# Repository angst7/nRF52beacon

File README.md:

#nRF52beacon#

nRF52832 based beacon design

Simple reference design in a 1"x1.2" form factor with CR2032 battery holder.  For maximum battery life, ditch protection 
diode D2 and replace it with a FET (or just a jumper).  Tested to work with examples from the nRF52 SDK v11.0.0, but no
guarantees as to the effectiveness of the antenna.  

##License##

This work is licensed under [CC Attribution 3.0 United States](https://creativecommons.org/licenses/by/3.0/us/).

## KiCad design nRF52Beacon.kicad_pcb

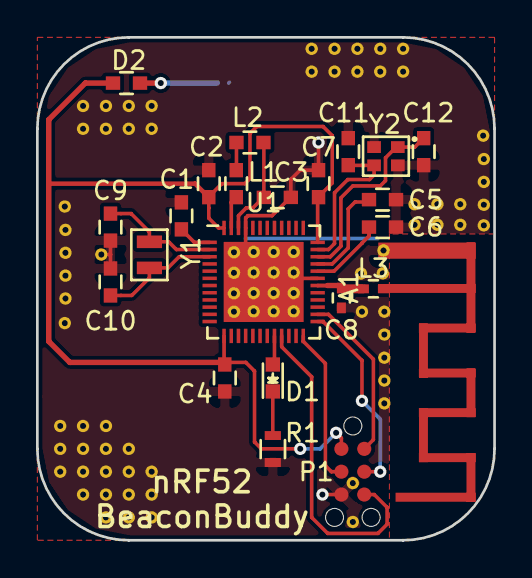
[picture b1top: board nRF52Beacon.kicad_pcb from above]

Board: 2 copper layers, 25.4 x 27.9 mm, 24 parts (1 on the bottom side), 21 nets.

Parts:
A1: Antenna; Antenna-2.45GHZ
BT1: BAT-HLD-001; BATT-HLD-001
C1, C4, C7: 0.1uF; C_0603
C2: 4.7uF; C_0603
C3: 1uF; C_0603
C5: 100pF; C_0603
C6: NC; C_0603
C8: 0.8pF; C_0402
C9, C10, C11, C12: 12pF; C_0603
D1: L0603G; LED_0603
D2: CDBU0240; C_0603
L1: 10uH; C_0603
L2: 15nH; C_0603
L3: 3.9nH; C_0402
P1: CONN_01X06; TC2030-MCP-NL
R1: 470; R_0603
U1: nRF52832-QFAA; UQFN-48-1EP_6x6mm_Pitch0.4mm
Y1: 32.768kHz; Crystal_ABS06
Y2: 32MHz; Crystal_ABM11

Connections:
/ANT: C8.1, L3.2, U1.30
/RF_OUT: A1.1, L3.1
/SWDCLK: P1.4, U1.25
/SWDIO: P1.2, U1.26
/SWO: P1.6, U1.21
/XC1: C11.2, U1.35, Y2.3
/XC2: C12.2, U1.34, Y2.1
/XL1: C9.2, U1.2, Y1.1
/XL2: C10.2, U1.3, Y1.2
/nRESET: P1.3, U1.24
GND: A1.2, BT1.2, C1.2, C2.2, C3.2, C4.2, C5.1, C6.1, C7.2, C8.2, C9.1, C10.1, C11.1, C12.1, P1.5, R1.2, U1.31, U1.45, U1.49, Y2.2, Y2.4
unnamed: BT1.1, D2.2
unnamed: C1.1, U1.1
unnamed: C3.1, L2.1, U1.46
unnamed: C5.2, U1.33
unnamed: C6.2, U1.32
unnamed: D1.1, R1.1
unnamed: D1.2, U1.20
unnamed: L1.1, L2.2
unnamed: L1.2, U1.47
VDD: C2.1, C4.1, C7.1, D2.1, P1.1, U1.13, U1.36, U1.48

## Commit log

2016-07-16 Initial Commit, Revision 1
2016-08-10 Removed paste from TC2030 pads
2016-08-10 add readme
